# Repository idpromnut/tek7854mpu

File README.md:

# tek7854mpu
Tools for debugging and working with the Tek7854 microprocessor board.

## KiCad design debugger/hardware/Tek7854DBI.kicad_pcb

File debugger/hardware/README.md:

# MojoV2 Adapter Design Files
Note that the hardware for this project uses two external libraries:

https://github.com/cpavlina/kicad-pcblib
https://github.com/cpavlina/kicad-schlib

All the symbols should be cached in the porject however, f you just want to look at it and do small modifications.

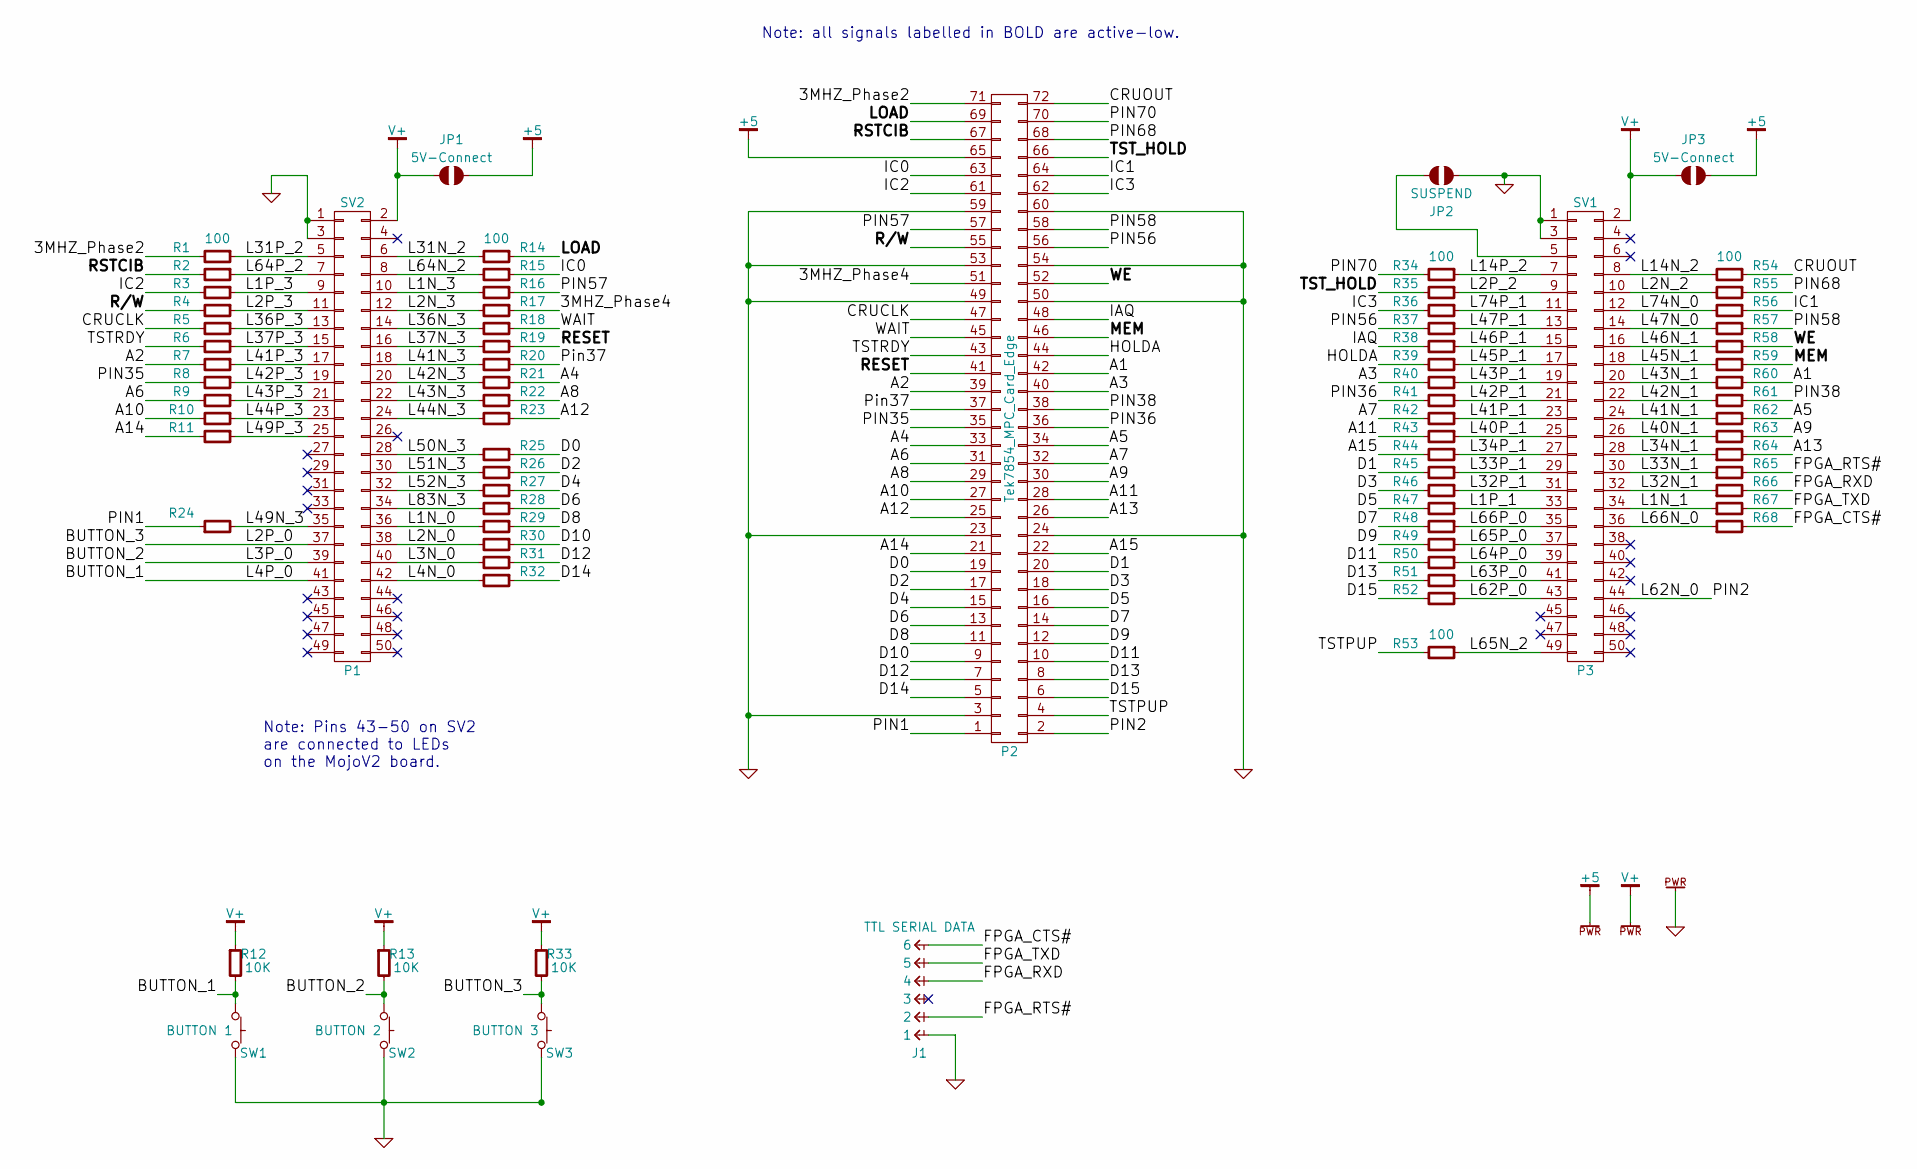
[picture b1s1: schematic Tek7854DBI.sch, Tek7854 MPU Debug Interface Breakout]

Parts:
J1: TTL SERIAL DATA; CONN-100MIL-M-1x6
JP1, JP3: 5V-Connect; JUMPER-SOLDER-SMD
JP2: SUSPEND; JUMPER-SOLDER-SMD
P1: SV2; CONN-100MIL-M-2x25
P2: Tek7854_MPC_Card_Edge; CONN-TE-5530843-8-F-2x36
P3: SV1; CONN-100MIL-M-2x25
R1, R2, R3, R4, R5, R6, R7, R8, R9, R10, R11, R14, R15, R16, R17, R18, R19, R20, R21, R22, R23, R24, R25, R26, R27, R28, R29, R30, R31, R32, R34, R35, R36, R37, R38, R39, R40, R41, R42, R43, R44, R45, R46, R47, R48, R49, R50, R51, R52, R53, R54, R55, R56, R57, R58, R59, R60, R61, R62, R63, R64, R65, R66, R67, R68: 100; R_0603_HandSoldering
R12, R13, R33: 10K; R_0603_HandSoldering
SW1: BUTTON 1; TE-FSMSM
SW2: BUTTON 2; TE-FSMSM
SW3: BUTTON 3; TE-FSMSM

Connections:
/3MHZ_Phase2: P2.71, R1.2
/3MHZ_Phase4: P2.51, R17.1
/A1: P2.42, R60.1
/A2: P2.39, R7.2
/A3: P2.40, R40.2
/A4: P2.33, R21.1
/A5: P2.34, R62.1
/A6: P2.31, R9.2
/A7: P2.32, R42.2
/A8: P2.29, R22.1
/A9: P2.30, R63.1
/A10: P2.27, R10.2
/A11: P2.28, R43.2
/A12: P2.25, R23.1
/A13: P2.26, R64.2
/A14: P2.21, R11.2
/A15: P2.22, R44.2
/BUTTON_1: P1.41, R12.2, SW1.1
/BUTTON_2: P1.39, R13.2, SW2.1
/BUTTON_3: P1.37, R33.2, SW3.1
/CRUCLK: P2.47, R5.2
/CRUOUT: P2.72, R54.1
/D0: P2.19, R25.1
/D1: P2.20, R45.2
/D2: P2.17, R26.1
/D3: P2.18, R46.2
/D4: P2.15, R27.1
/D5: P2.16, R47.2
/D6: P2.13, R28.1
/D7: P2.14, R48.2
/D8: P2.11, R29.1
/D9: P2.12, R49.2
/D10: P2.9, R30.1
/D11: P2.10, R50.2
/D12: P2.7, R31.1
/D13: P2.8, R51.2
/D14: P2.5, R32.1
/D15: P2.6, R52.2
/FPGA_CTS#: J1.6, R68.2
/FPGA_RTS#: J1.2, R65.2
/FPGA_RXD: J1.4, R66.2
/FPGA_TXD: J1.5, R67.2
/HOLDA: P2.44, R39.2
/IAQ: P2.48, R38.2
/IC0: P2.63, R15.1
/IC1: P2.64, R56.1
/IC2: P2.61, R3.2
/IC3: P2.62, R36.2
/L1N_0: P1.36, R29.2
/L1N_1: P3.34, R67.1
/L1N_3: P1.10, R16.2
/L1P_1: P3.33, R47.1
/L1P_3: P1.9, R3.1
/L2N_0: P1.38, R30.2
/L2N_2: P3.10, R55.2
/L2N_3: P1.12, R17.2
/L2P_2: P3.9, R35.1
/L2P_3: P1.11, R4.1
/L3N_0: P1.40, R31.2
/L4N_0: P1.42, R32.2
/L14N_2: P3.8, R54.2
/L14P_2: P3.7, R34.1
/L31N_2: P1.6, R14.2
/L31P_2: P1.5, R1.1
/L32N_1: P3.32, R66.1
/L32P_1: P3.31, R46.1
/L33N_1: P3.30, R65.1
/L33P_1: P3.29, R45.1
/L34N_1: P3.28, R64.1
/L34P_1: P3.27, R44.1
/L36N_3: P1.14, R18.2
/L36P_3: P1.13, R5.1
/L37N_3: P1.16, R19.2
/L37P_3: P1.15, R6.1
/L40N_1: P3.26, R63.2
/L40P_1: P3.25, R43.1
/L41N_1: P3.24, R62.2
/L41N_3: P1.18, R20.2
/L41P_1: P3.23, R42.1
/L41P_3: P1.17, R7.1
/L42N_1: P3.22, R61.2
/L42N_3: P1.20, R21.2
/L42P_1: P3.21, R41.1
/L42P_3: P1.19, R8.1
/L43N_1: P3.20, R60.2
/L43N_3: P1.22, R22.2
/L43P_1: P3.19, R40.1
/L43P_3: P1.21, R9.1
/L44N_3: P1.24, R23.2
/L44P_3: P1.23, R10.1
/L45N_1: P3.18, R59.2
/L45P_1: P3.17, R39.1
/L46N_1: P3.16, R58.2
/L46P_1: P3.15, R38.1
/L47N_0: P3.14, R57.2
/L47P_1: P3.13, R37.1
/L49N_3: P1.35, R24.2
/L49P_3: P1.25, R11.1
/L50N_3: P1.28, R25.2
/L51N_3: P1.30, R26.2
/L52N_3: P1.32, R27.2
/L62N_0: P2.2, P3.44
/L62P_0: P3.43, R52.1
/L63P_0: P3.41, R51.1
/L64N_2: P1.8, R15.2
/L64P_0: P3.39, R50.1
/L64P_2: P1.7, R2.1
/L65N_2: P3.49, R53.1
/L65P_0: P3.37, R49.1
/L66N_0: P3.36, R68.1
/L66P_0: P3.35, R48.1
/L74N_0: P3.12, R56.2
/L74P_1: P3.11, R36.1
/L83N_3: P1.34, R28.2
/LOAD: P2.69, R14.1
/MEM: P2.46, R59.1
/PIN1: P2.1, R24.1
/PIN35: P2.35, R8.2
/PIN36: P2.36, R41.2
/PIN38: P2.38, R61.1
/PIN56: P2.56, R37.2
/PIN57: P2.57, R16.1
/PIN58: P2.58, R57.1
/PIN68: P2.68, R55.1
/PIN70: P2.70, R34.2
/Pin37: P2.37, R20.1
/R/W: P2.55, R4.2
/RESET: P2.41, R19.1
/RSTCIB: P2.67, R2.2
/TSTPUP: P2.4, R53.2
/TSTRDY: P2.43, R6.2
/TST_HOLD: P2.66, R35.2
/WAIT: P2.45, R18.1
/WE: P2.52, R58.1
unnamed: JP2.2, P3.5

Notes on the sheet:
Note: all signals labelled in BOLD are active-low.
Note: Pins 43-50 on SV2 are connected to LEDs on the MojoV2 board.

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
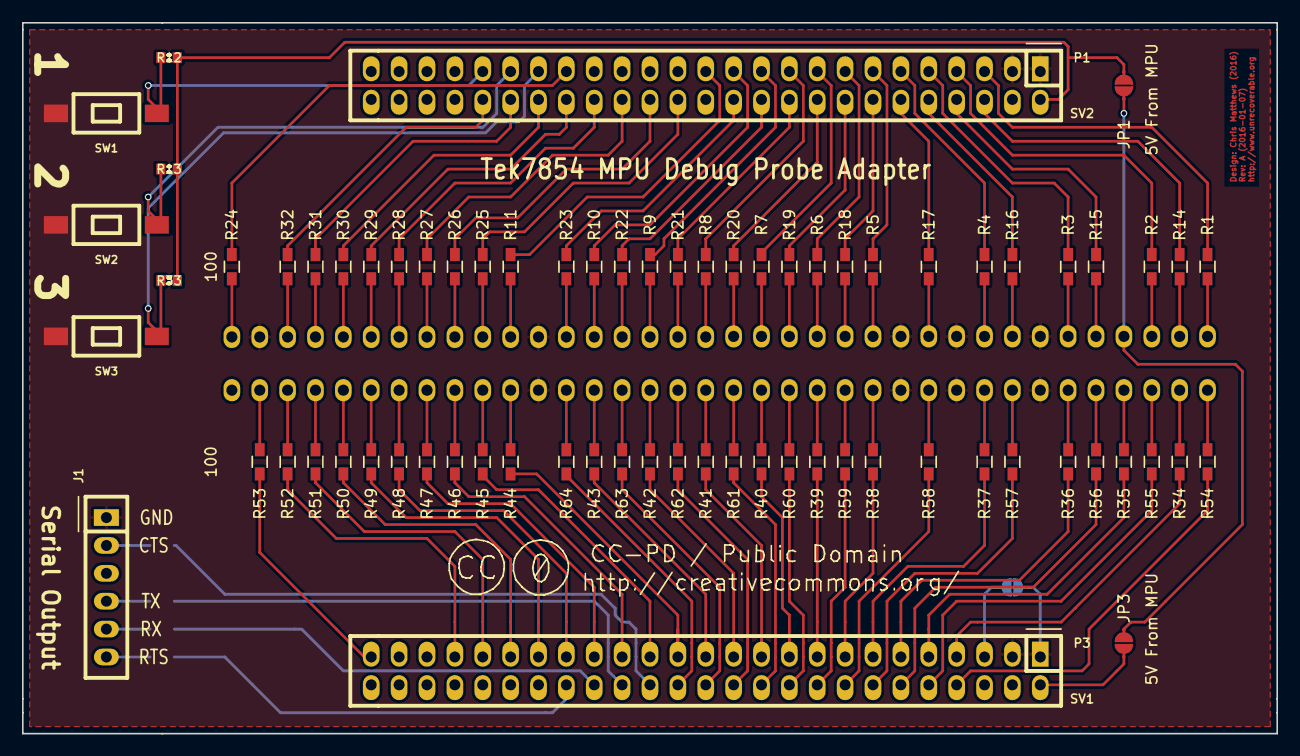
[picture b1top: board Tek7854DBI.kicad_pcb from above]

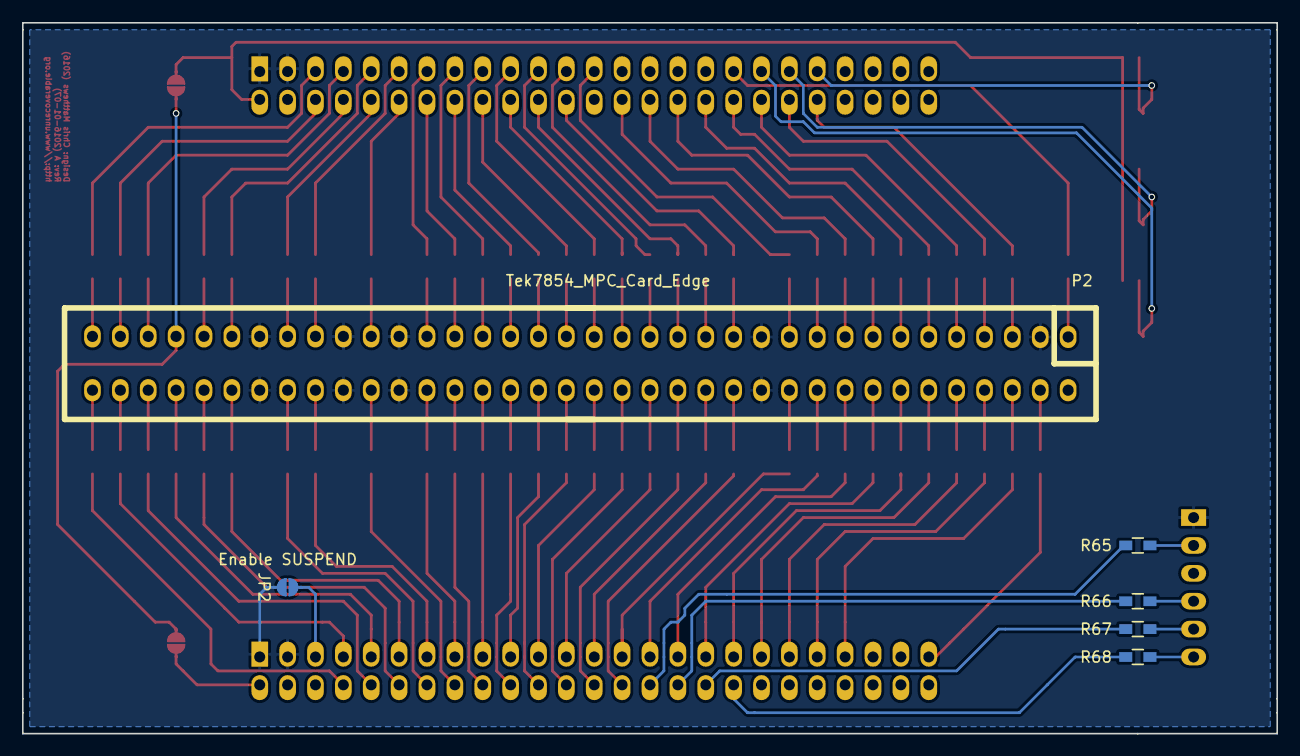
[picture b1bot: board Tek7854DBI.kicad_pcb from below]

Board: 2 copper layers, 114.3 x 64.8 mm, 78 parts (6 on the bottom side), 138 nets.

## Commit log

2016-01-14 Hardware added
    Added interface board PCB design files. This supports a MojoV2
    interfaced directly to the Tek7854 MPU debugging card edge header.
2016-01-16 Added readme to hardware directory
2016-01-30 Add initial HDL project
2016-01-31 Add test serial transmitter
2016-02-29 NET naming error
    IC1 and IC3 had incorrect net names.
2016-08-16 Experimenting with I/O lines
2016-09-20 Added service manual and IC datasheets
2016-09-22 Added schematic-only PDF for the Tek 7854.
2016-10-10 Adding ROM images for the Tek 7854
2017-05-02 Added placeholder for rom board reader firmware.
2017-05-14 Removed rom images
